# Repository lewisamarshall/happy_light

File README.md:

Happy Light
===========
A custom wake-up light PCB and arduino code. 

Lights
------
Intended for use with [Adafruit RGBW LED Strip](https://www.adafruit.com/product/2439?length=4). 
These run at 12 V, and draw up to 1.6A/meter, or 400 mA/meter per color.

Power
-----
The board is intended to run on 12V power input (both microcontroller and LED power).
For a full spool (4m) of the lights above, this could be about 80W total.
Power is controlled by 4x TO-3 darlington power transistors.

Control
=======
This is designed for an Arduino Nano. The firmware assumes a Nano 33 IOT, to get network time.

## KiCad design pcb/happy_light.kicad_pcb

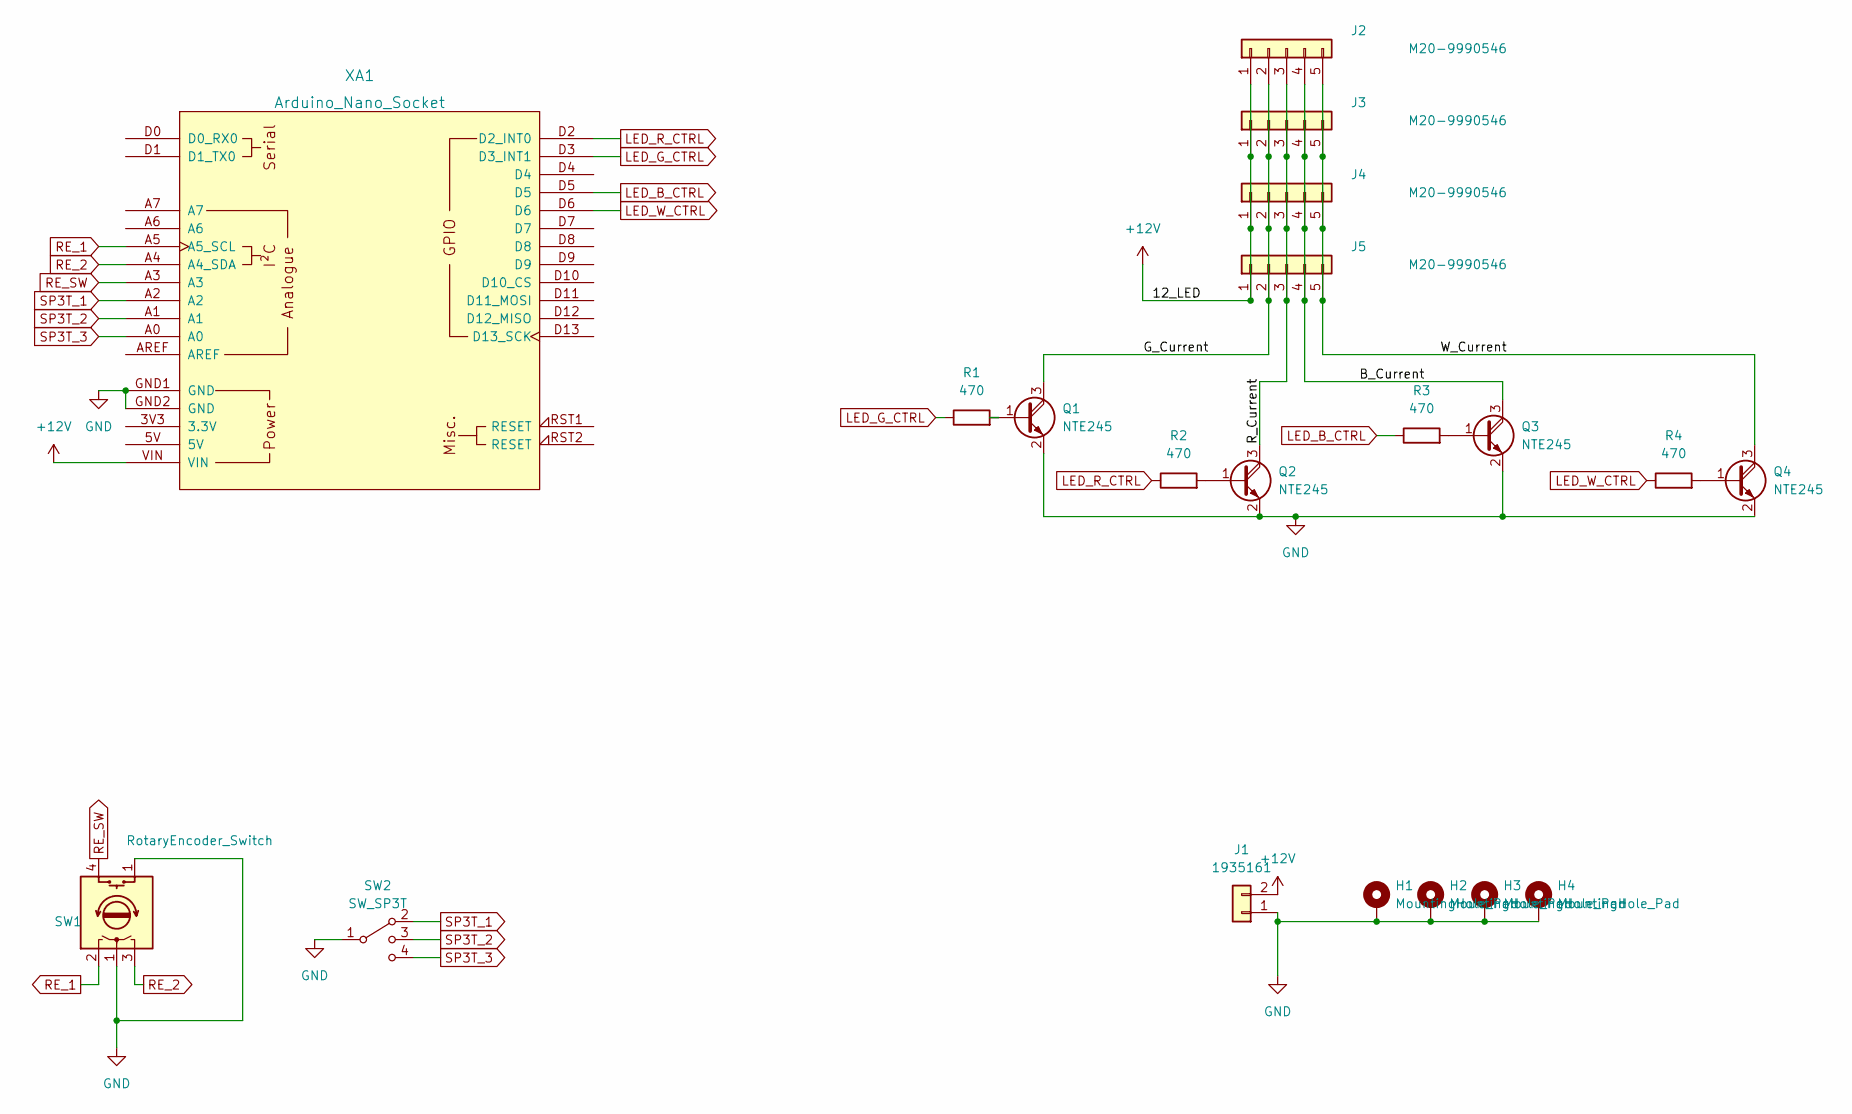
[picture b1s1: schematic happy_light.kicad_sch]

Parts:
H1, H2, H3, H4: MountingHole_Pad; MountingHole_3.2mm_M3_Pad
J1: 1935161; TerminalBlock_Phoenix_MKDS-1,5-2_1x02_P5.00mm_Horizontal
J2, J3, J4, J5: M20-9990546; PinHeader_1x05_P2.54mm_Vertical
Q1, Q2, Q3, Q4: NTE245; TO-3
R1, R2, R3, R4: 470; R_Axial_DIN0207_L6.3mm_D2.5mm_P7.62mm_Horizontal
SW1: RotaryEncoder_Switch; PinHeader_1x04_P2.54mm_Vertical
SW2: SW_SP3T; PinHeader_1x04_P2.54mm_Vertical
XA1: Arduino_Nano_Socket

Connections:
+12V: J1.2, J2.1, J3.1, J4.1, J5.1, XA1.VIN
/B_Current: J2.4, J3.4, J4.4, J5.4, Q3.3 (C)
/G_Current: J2.2, J3.2, J4.2, J5.2, Q1.3 (C)
/R_Current: J2.3, J3.3, J4.3, J5.3, Q2.3 (C)
/W_Current: J2.5, J3.5, J4.5, J5.5, Q4.3 (C)
GND: H1.1, H2.1, H3.1, H4.1, J1.1, Q1.2 (E), Q2.2 (E), Q3.2 (E), Q4.2 (E), SW1.1 (C), SW2.1 (3), XA1.GND1 (GND), XA1.GND2 (GND)
LED_B_CTRL: R3.1, XA1.D5
LED_G_CTRL: R1.1, XA1.D3 (D3_INT1)
LED_R_CTRL: R2.1, XA1.D2 (D2_INT0)
LED_W_CTRL: R4.1, XA1.D6
unnamed: Q1.1 (B), R1.2
unnamed: Q2.1 (B), R2.2
unnamed: Q3.1 (B), R3.2
unnamed: Q4.1 (B), R4.2
RE_1: SW1.2 (A), XA1.A5 (A5_SCL)
RE_2: SW1.3 (B), XA1.A4 (A4_SDA)
RE_SW: SW1.4 (S1), XA1.A3
SP3T_1: SW2.2 (1), XA1.A2
SP3T_2: SW2.3 (2), XA1.A1
SP3T_3: SW2.4, XA1.A0

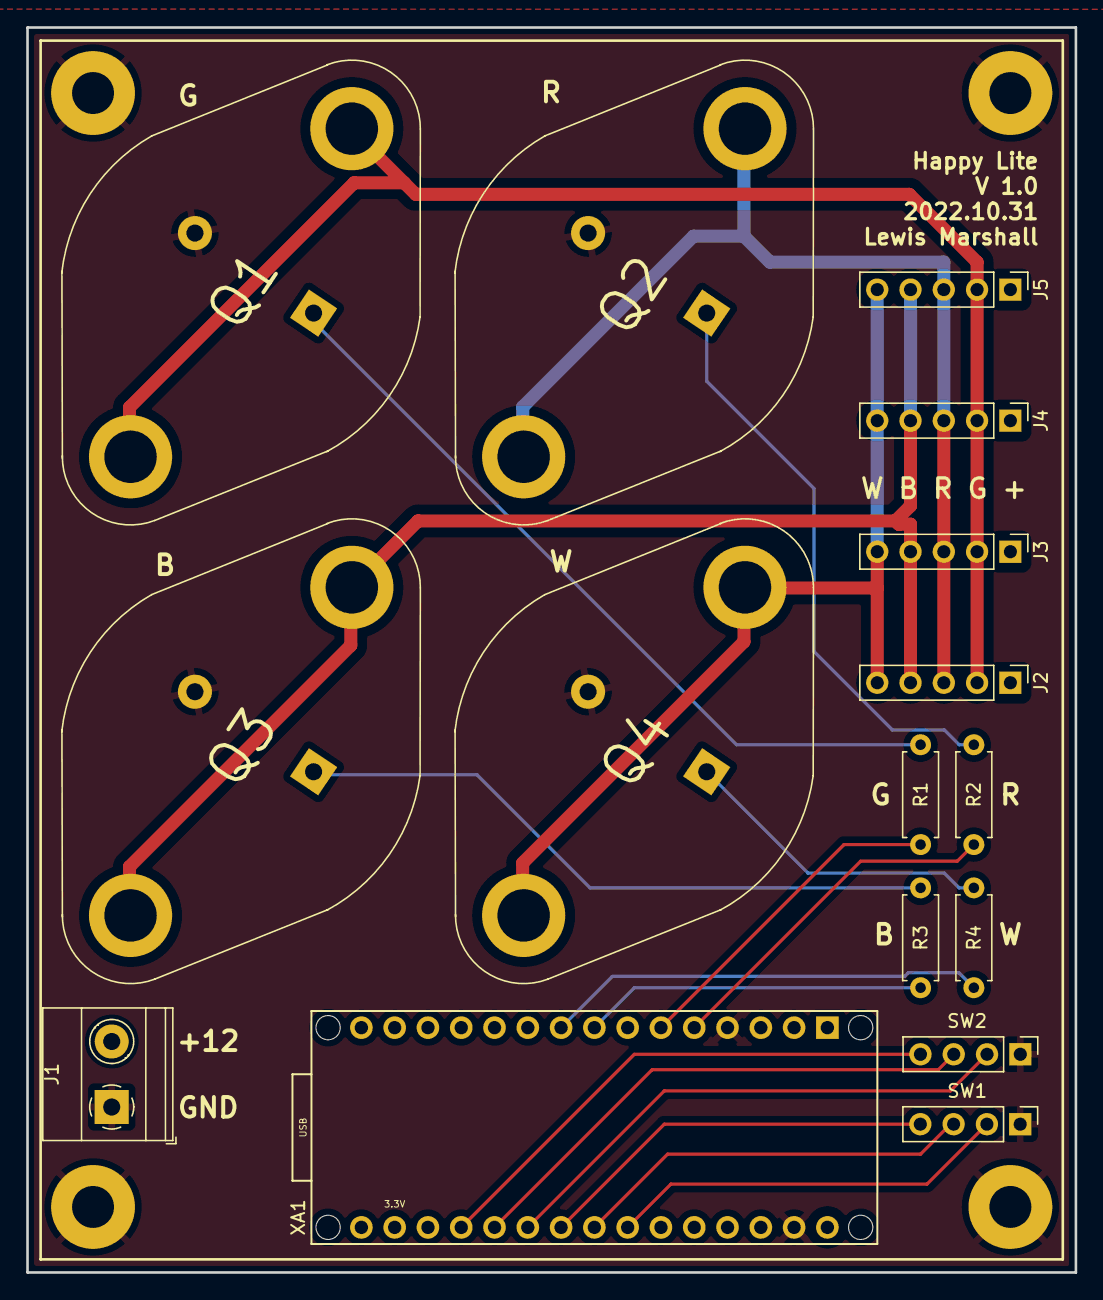
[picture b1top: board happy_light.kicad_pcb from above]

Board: 2 copper layers, 80.0 x 95.0 mm, 20 parts (0 on the bottom side), 20 nets.

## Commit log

2022-11-05 Initial commit.
2022-11-07 Changed for DLT.
2022-11-14 updated light order for PCB.
2022-11-14 Added PCB design.
2025-01-27 Update.
